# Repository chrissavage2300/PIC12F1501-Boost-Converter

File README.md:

6/24/2022 - updated PIC to show correct part number

# PIC12F1501-Boost-Converter
A circuit based on appnote TB3102

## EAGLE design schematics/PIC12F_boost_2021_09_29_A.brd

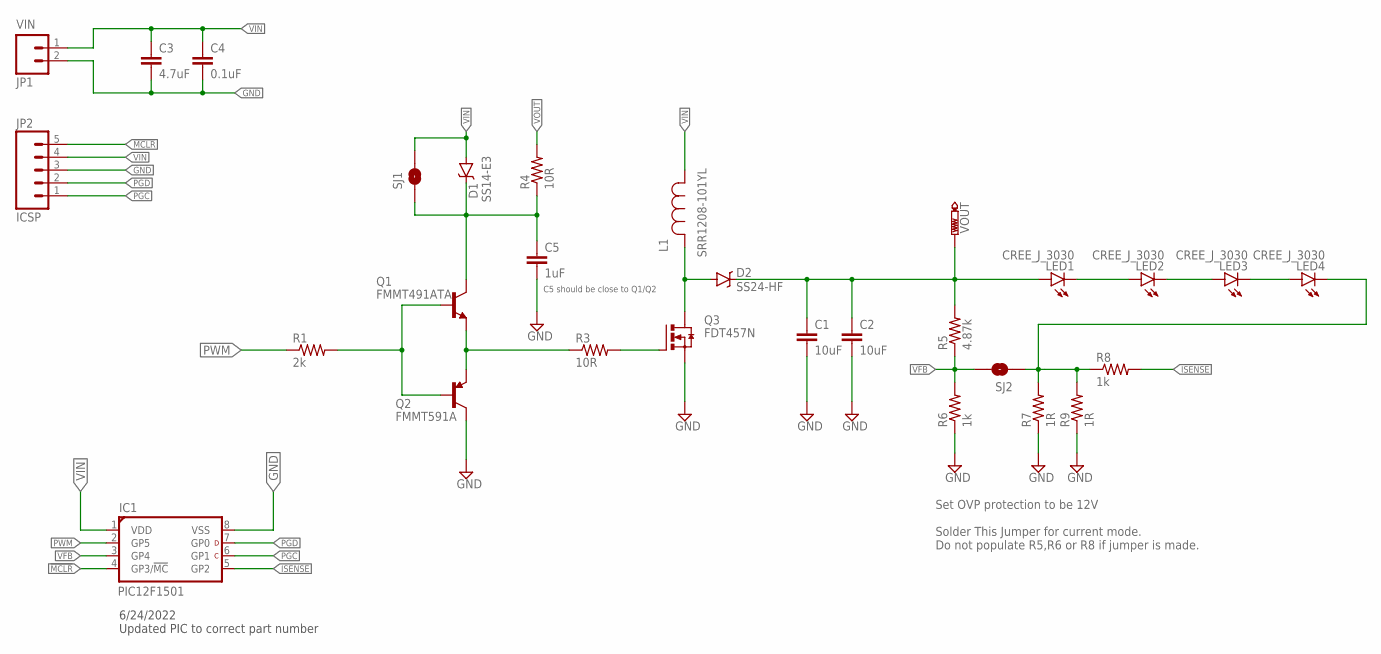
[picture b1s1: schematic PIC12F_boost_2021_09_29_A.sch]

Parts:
C1, C2: 10uF; 1206
C3: 4.7uF; 1206
C4: 0.1uF; 1206
C5: 1uF; 1206
D1: SS14-E3; SOD-323
D2: SS24-HF; SMA-DIODE
IC1: PIC12F1501; SOIC8-SN
JP1: M02POLAR_LOCK; MOLEX-1X2_LOCK
JP2: ICSP; 1X05_LOCK_LONGPADS
L1: SRR1208-101YL; IND_BOURNS_SRR1208
LED1, LED2, LED3, LED4: CREE_J_3030
Q1: FMMT491ATA; SOT23
Q2: FMMT591A; SOT23
Q3: FDT457N; SOT223
R1: 2k; 1206
R3, R4: 10R; 1206
R5: 4.87k; 1206
R6, R8: 1k; 1206
R7, R9: 1R; 1206
SJ1, SJ2: SPARKFUN_SOLDERJUMPERNO; SPARKFUN_SJ_2S-NO
VOUT: PTR1TP20R; TP20R

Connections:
!MCLR: IC1.4 (GP3/!MC!), JP2.5
DRIVE: Q1.2 (E), Q2.2 (E), R3.1
GATE: Q3.1 (G), R3.2
GND: C1.2, C2.2, C3.2, C4.2, C5.2, IC1.8 (VSS), JP1.2, JP2.3, Q2.3 (C), Q3.3 (S), R6.1, R7.1, R9.1
ISENSE: IC1.5 (GP2), R8.2
unnamed: Q1.1 (B), Q2.1 (B), R1.2
unnamed: C5.1, D1.C, Q1.3 (C), R4.1, SJ1.1
unnamed: LED1.C, LED2.A, LED2.A2 (A)
unnamed: LED2.C, LED3.A, LED3.A2 (A)
unnamed: LED3.C, LED4.A, LED4.A2 (A)
PGC: IC1.6 (GP1), JP2.1
PGD: IC1.7 (GP0), JP2.2
PWM: IC1.2 (GP5), R1.1
SW: D2.A, L1.2, Q3.4 (D)
VFB: IC1.3 (GP4), R5.1, R6.2, SJ2.2
VIN: C3.1, C4.1, D1.A, IC1.1 (VDD), JP1.1, JP2.4, L1.1, SJ1.2
VOUT: C1.1, C2.1, D2.C, LED1.A, LED1.A2 (A), R4.2, R5.2, VOUT.TP
VOUT-: LED4.C, R7.2, R8.1, R9.2, SJ2.1

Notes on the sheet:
C5 should be close to Q1/Q2
VIN
Set OVP protection to be 12V Solder This Jumper for current mode. Do not populate R5,R6 or R8 if jumper is made.
6/24/2022 Updated PIC to correct part number

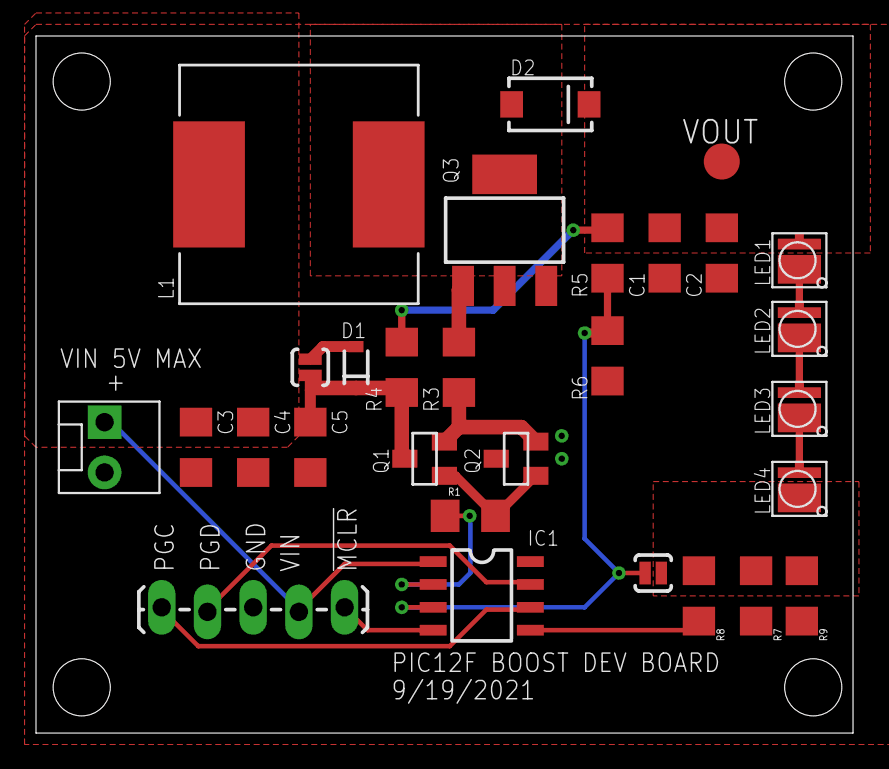
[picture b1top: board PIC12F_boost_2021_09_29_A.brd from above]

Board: 2 copper layers, 45.4 x 38.7 mm, 29 parts (0 on the bottom side), 18 nets.

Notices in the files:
parts and their libraries:
SparkFun-Capacitors: Licensing: Creative Commons ShareAlike 4.0 International - https://creativecommons.org/licenses/by-sa/4.0
COPYRIGHT: Copyright (C) 2021 Ultra Librarian. All rights reserved.
